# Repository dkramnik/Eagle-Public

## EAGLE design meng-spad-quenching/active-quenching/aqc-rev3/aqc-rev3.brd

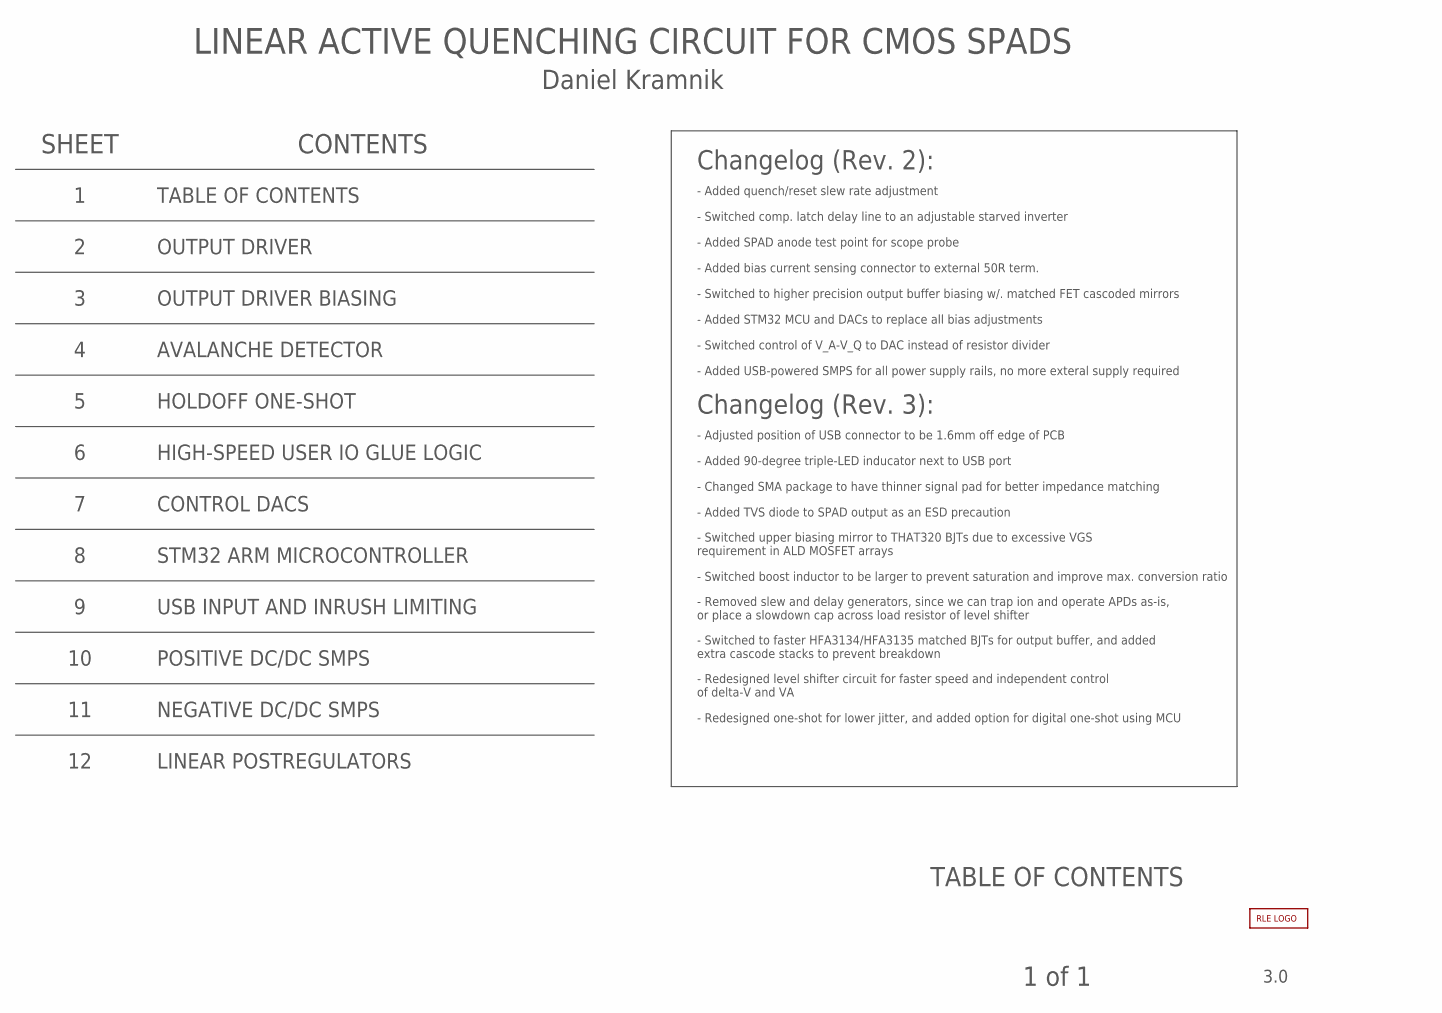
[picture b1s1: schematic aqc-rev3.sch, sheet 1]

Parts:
DNP1000: RLE_LOGO

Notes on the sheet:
Changelog (Rev. 2):
- Added quench/reset slew rate adjustment
- Switched comp. latch delay line to an adjustable starved inverter
- Added SPAD anode test point for scope probe
- Added bias current sensing connector to external 50R term.
- Added USB-powered SMPS for all power supply rails, no more exteral supply required
- Added STM32 MCU and DACs to replace all bias adjustments
- Switched to higher precision output buffer biasing w/. matched FET cascoded mirrors
- Switched control of V_A-V_Q to DAC instead of resistor divider
TABLE OF CONTENTS
3.0
1 of 1
LINEAR ACTIVE QUENCHING CIRCUIT FOR CMOS SPADS
SHEET
CONTENTS
Daniel Kramnik
OUTPUT DRIVER
OUTPUT DRIVER BIASING
STM32 ARM MICROCONTROLLER
CONTROL DACS
AVALANCHE DETECTOR
POSITIVE DC/DC SMPS
NEGATIVE DC/DC SMPS
USB INPUT AND INRUSH LIMITING
HOLDOFF ONE-SHOT
LINEAR POSTREGULATORS
Changelog (Rev. 3):
- Adjusted position of USB connector to be 1.6mm off edge of PCB
- Added 90-degree triple-LED inducator next to USB port
- Changed SMA package to have thinner signal pad for better impedance matching
- Added TVS diode to SPAD output as an ESD precaution
- Switched upper biasing mirror to THAT320 BJTs due to excessive VGS requirement in ALD MOSFET arrays
- Switched boost inductor to be larger to prevent saturation and improve max. conversion ratio
- Removed slew and delay generators, since we can trap ion and operate APDs as-is, or place a slowdown cap across load resistor of level shifter
- Switched to faster HFA3134/HFA3135 matched BJTs for output buffer, and added extra cascode stacks to prevent breakdown
- Redesigned level shifter circuit for faster speed and independent control of delta-V and VA
- Redesigned one-shot for lower jitter, and added option for digital one-shot using MCU
HIGH-SPEED USER IO GLUE LOGIC

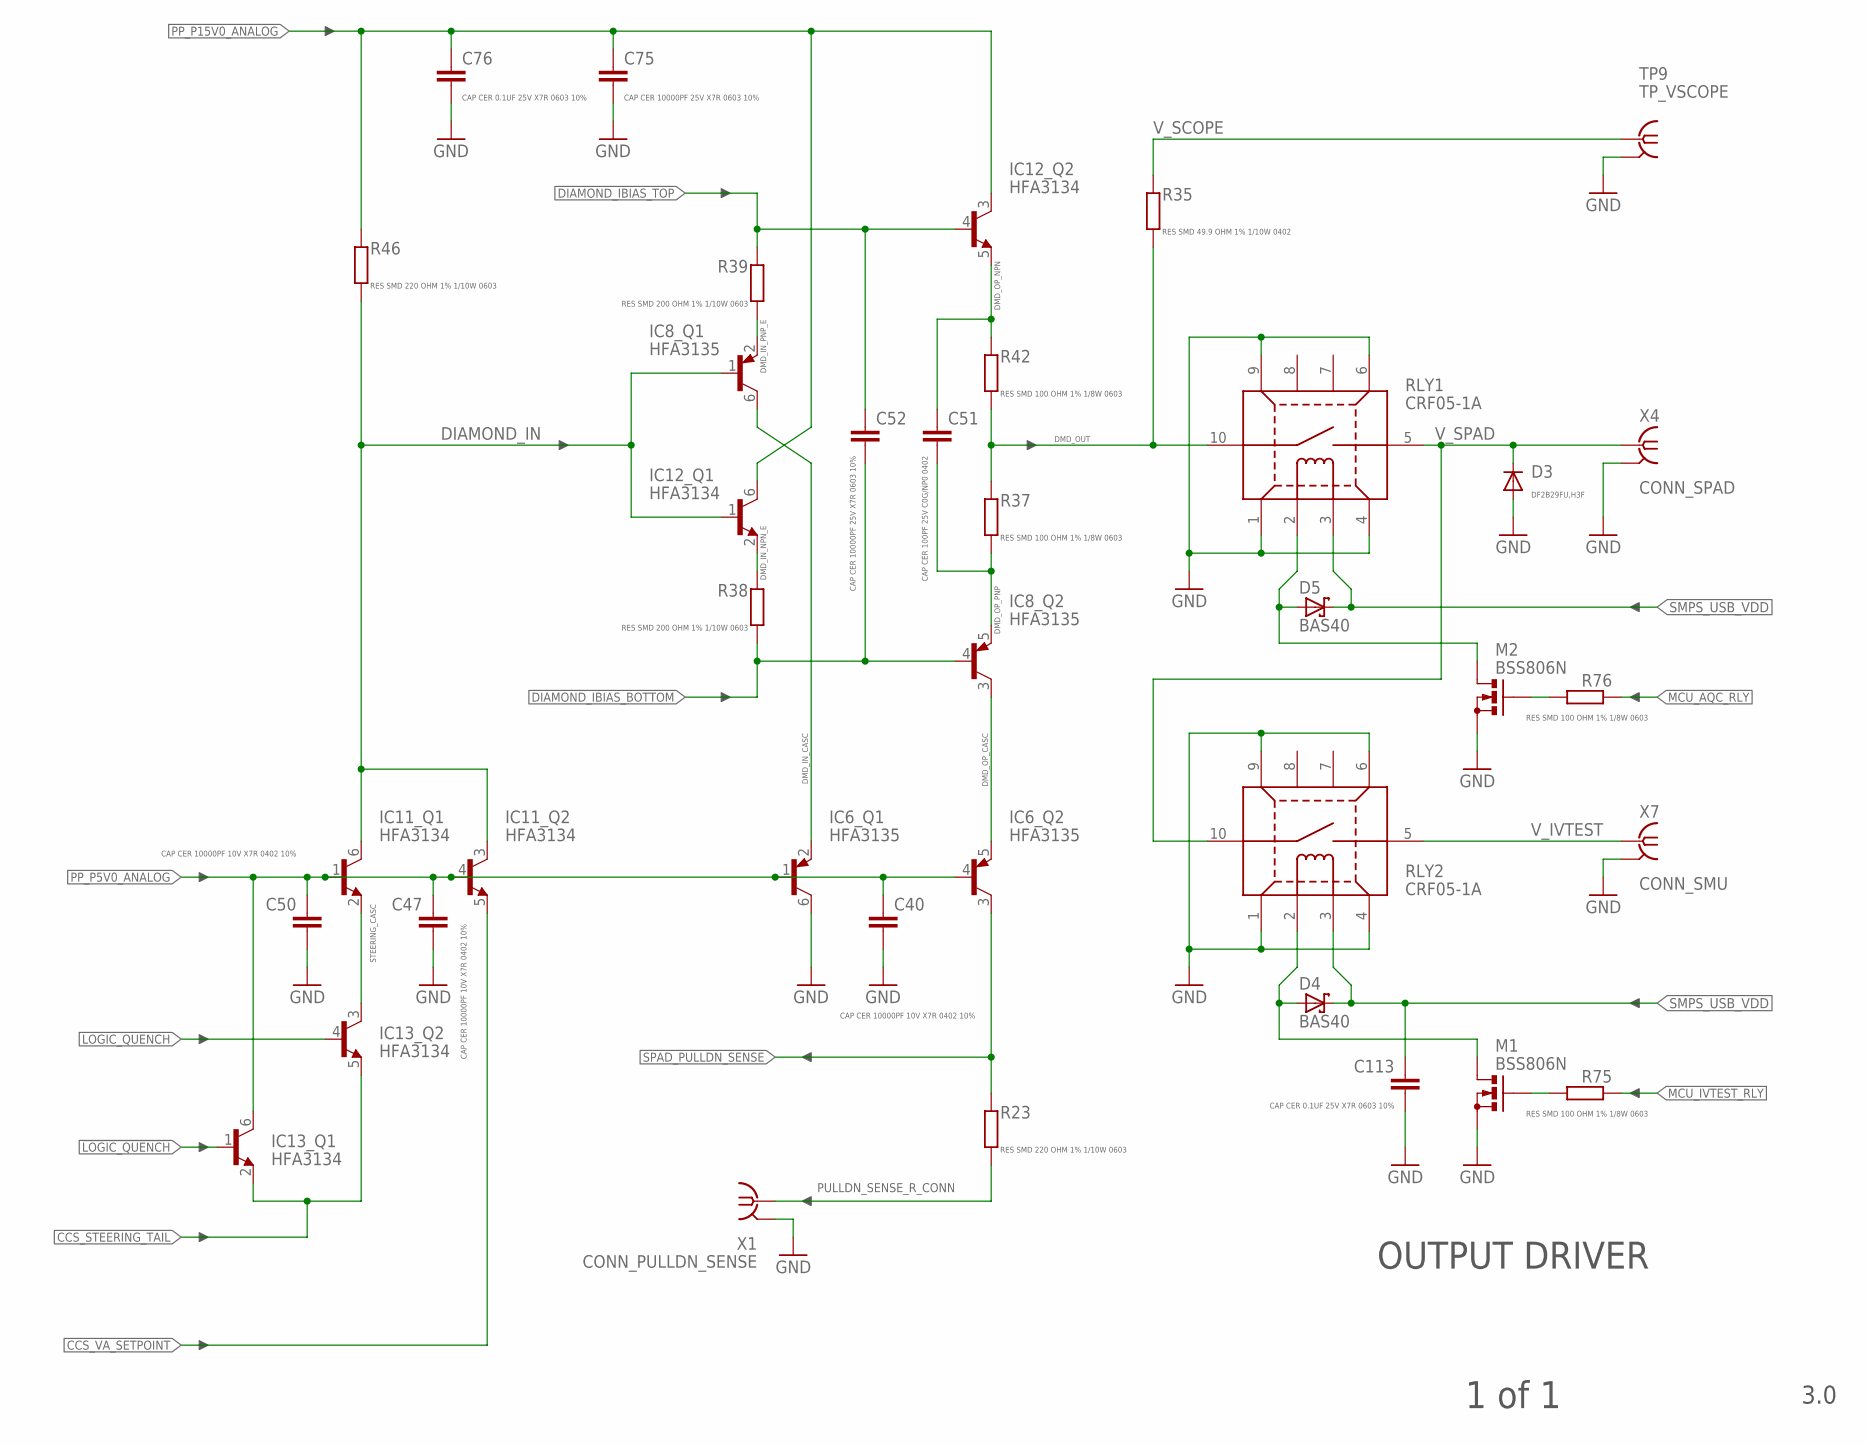
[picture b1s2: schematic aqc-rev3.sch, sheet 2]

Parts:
C40, C47, C50: CAP CER 10000PF 10V X7R 0402 10%; C0402
C51: CAP CER 100PF 25V C0G/NP0 0402; C0402
C52, C75: CAP CER 10000PF 25V X7R 0603 10%; C0603
C76, C113: CAP CER 0.1UF 25V X7R 0603 10%; C0603
D3: DF2B29FU,H3F; SOD523
D4, D5: BAS40; SOT23
IC6, IC8: HFA3135; SOT23-6L
IC11, IC12, IC13: HFA3134; SOT23-6L
M1, M2: BSS806N; SOT23R_INFINEON
R23, R46: RES SMD 220 OHM 1% 1/10W 0603; R0603
R35: RES SMD 49.9 OHM 1% 1/10W 0402; R0402
R37, R42, R75, R76: RES SMD 100 OHM 1% 1/8W 0603; R0603
R38, R39: RES SMD 200 OHM 1% 1/10W 0603; R0603
RLY1, RLY2: CRF05-1A; MEDER_RELAY_CRF
TP9: TP_VSCOPE; JOHNSON-129-0701-30X
X1: CONN_PULLDN_SENSE; J502-ND-142-0701-881/886; MPN 142-0711-871
X4: CONN_SPAD; J502-ND-142-0701-881/886
X7: CONN_SMU; J502-ND-142-0701-881/886

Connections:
!LOGIC_QUENCH: IC13.1 (B); also elsewhere on the board
CCS_STEERING_TAIL: IC13.2 (E), IC13.5 (E); also elsewhere on the board
CCS_VA_SETPOINT: IC11.5 (E); also elsewhere on the board
DIAMOND_IBIAS_BOTTOM: C52.2, IC8.4 (B), R38.1; also elsewhere on the board
DIAMOND_IBIAS_TOP: C52.1, IC12.4 (B), R39.2; also elsewhere on the board
DIAMOND_IN: IC8.1 (B), IC11.3 (C), IC11.6 (C), IC12.1 (B), R46.1
DMD_IN_CASC: IC6.2 (E), IC8.6 (C)
DMD_IN_NPN_E: IC12.2 (E), R38.2
DMD_IN_PNP_E: IC8.2 (E), R39.1
DMD_OP_CASC: IC6.5 (E), IC8.3 (C)
DMD_OP_NPN: C51.1, IC12.5 (E), R42.2
DMD_OP_PNP: C51.2, IC8.5 (E), R37.1
DMD_OUT: R35.1, R37.2, R42.1, RLY1.10 (PIN10)
GND: C40.2, C47.2, C50.2, C75.2, C76.2, C113.2, D3.A, IC6.6 (C), M1.2 (S), M2.2 (S), RLY1.1 (PIN1), RLY1.4 (PIN4), RLY1.6 (PIN6), RLY1.9 (PIN9), RLY2.1 (PIN1), RLY2.4 (PIN4), RLY2.6 (PIN6), RLY2.9 (PIN9), TP9.GND1 (GND), TP9.GND2 (GND), X1.G@1 (GND), X1.G@2 (GND), X1.G@3 (GND), X1.G@4 (GND), X4.G@1 (GND), X4.G@2 (GND), X4.G@3 (GND), X4.G@4 (GND), X7.G@1 (GND), X7.G@2 (GND), X7.G@3 (GND), X7.G@4 (GND); also elsewhere on the board
LOGIC_QUENCH: IC13.4 (B); also elsewhere on the board
MCU_AQC_RLY: R76.2; also elsewhere on the board
MCU_IVTEST_RLY: R75.2; also elsewhere on the board
unnamed: M2.1 (G), R76.1
unnamed: D5.1 (A), M2.3 (D), RLY1.2 (PIN2)
unnamed: D4.1 (A), M1.3 (D), RLY2.2 (PIN2)
unnamed: M1.1 (G), R75.1
PP_P5V0_ANALOG: C40.1, C47.1, C50.1, IC6.1 (B), IC6.4 (B), IC11.1 (B), IC11.4 (B), IC13.6 (C); also elsewhere on the board
PP_P15V0_ANALOG: C75.1, C76.1, IC12.3 (C), IC12.6 (C), R46.2; also elsewhere on the board
PULLDN_SENSE_R_CONN: R23.1, X1.1
SMPS_USB_VDD: C113.1, D4.3 (C), D5.3 (C), RLY1.3 (PIN3), RLY2.3 (PIN3); also elsewhere on the board
SPAD_PULLDN_SENSE: IC6.3 (C), R23.2; also elsewhere on the board
STEERING_CASC: IC11.2 (E), IC13.3 (C)
V_IVTEST: RLY2.5 (PIN5), X7.1
V_SCOPE: R35.2, TP9.SIG (1)
V_SPAD: D3.C, RLY1.5 (PIN5), RLY2.10 (PIN10), X4.1

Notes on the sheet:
OUTPUT DRIVER
3.0
1 of 1

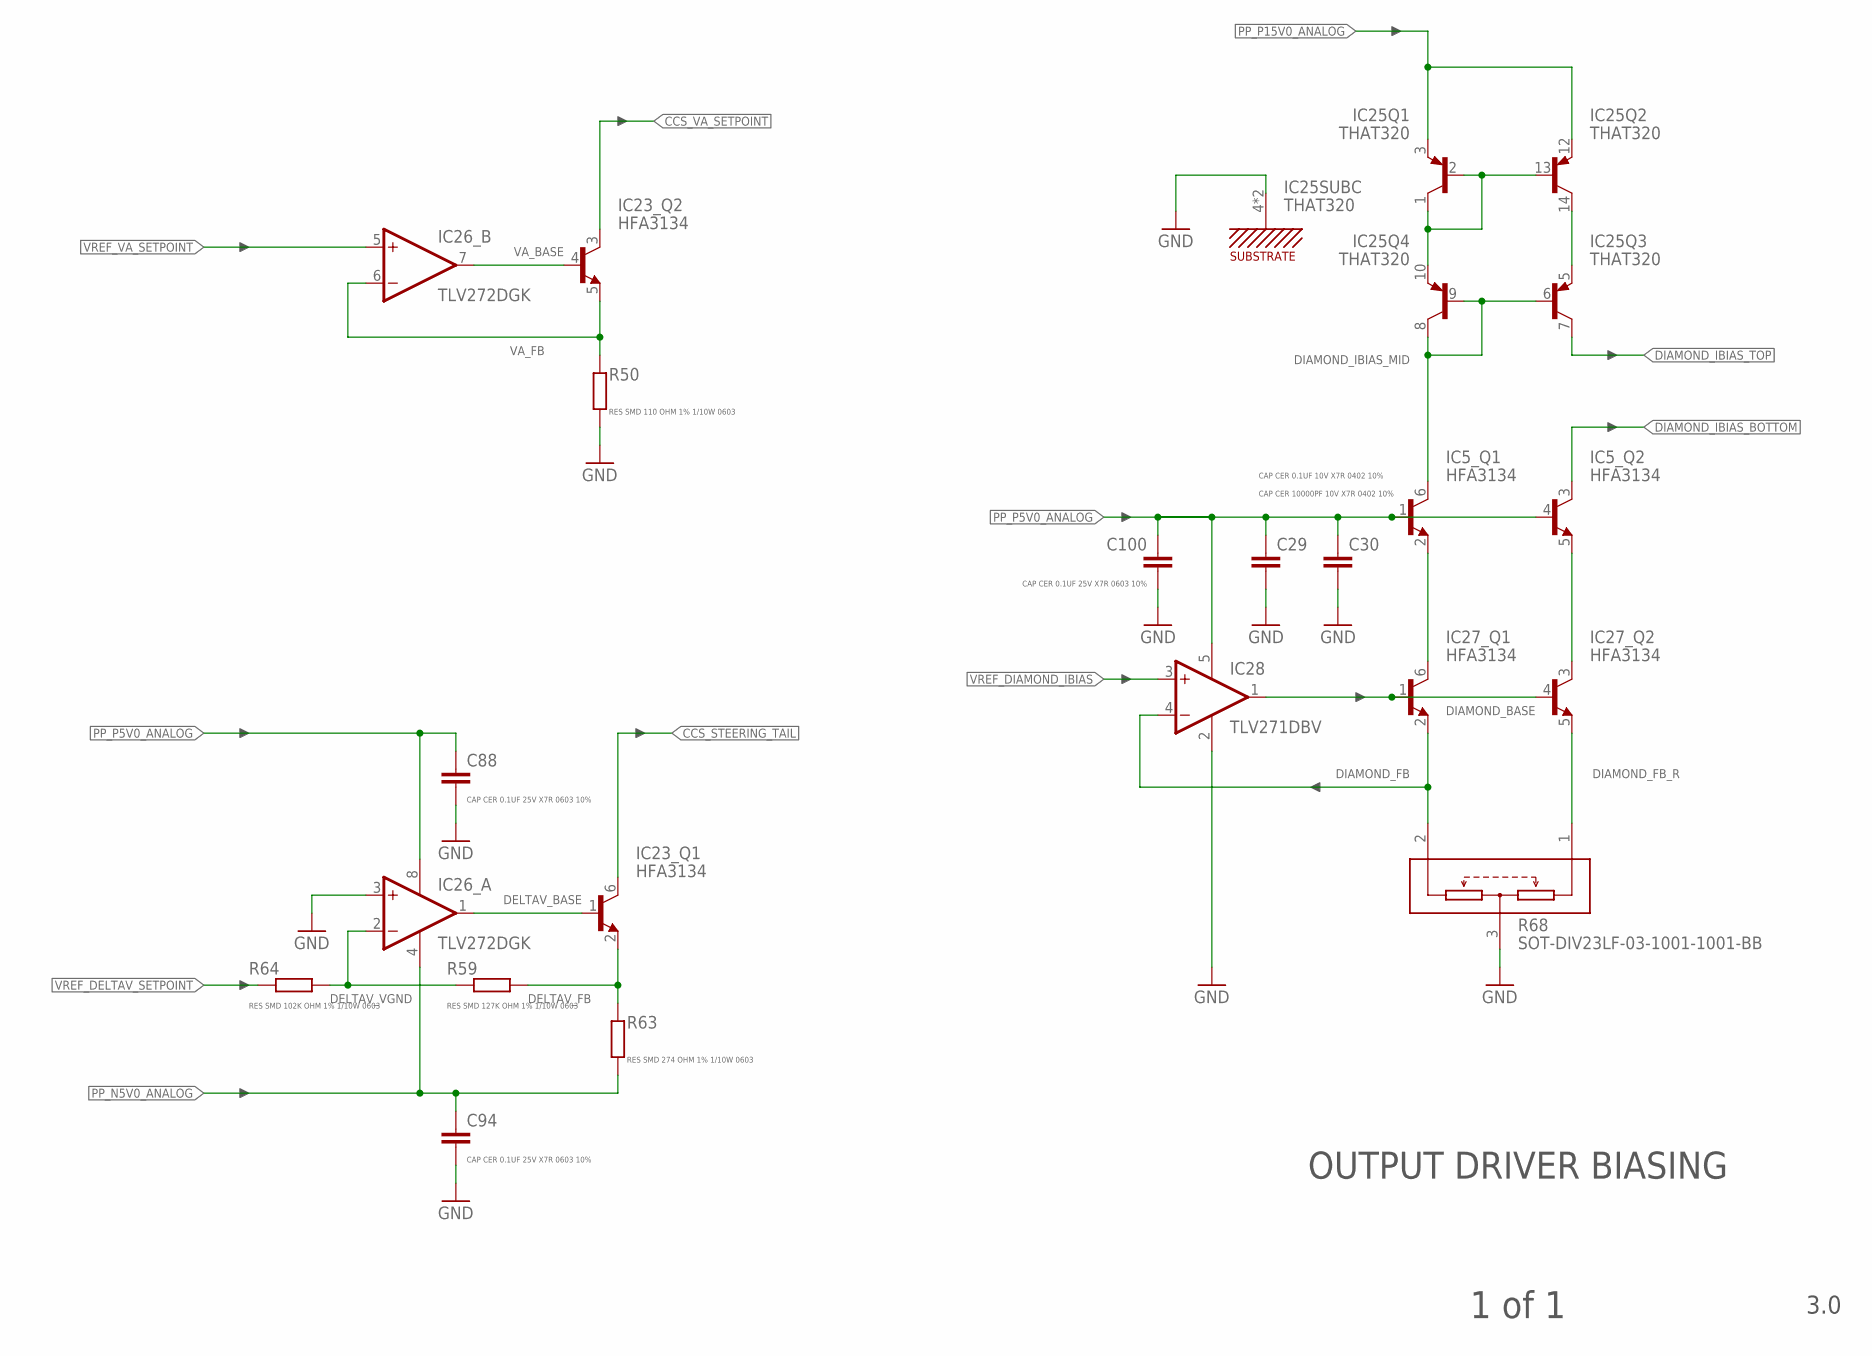
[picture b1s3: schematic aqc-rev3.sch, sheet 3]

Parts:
C29: CAP CER 0.1UF 10V X7R 0402 10%; C0402
C30: CAP CER 10000PF 10V X7R 0402 10%; C0402
C88, C94, C100: CAP CER 0.1UF 25V X7R 0603 10%; C0603
IC5, IC23, IC27: HFA3134; SOT23-6L
IC25: THAT320; SO14
IC26: TLV272DGK; MSOP8
IC28: TLV271DBV; SOT23-5
R50: RES SMD 110 OHM 1% 1/10W 0603; R0603
R59: RES SMD 127K OHM 1% 1/10W 0603; R0603
R63: RES SMD 274 OHM 1% 1/10W 0603; R0603
R64: RES SMD 102K OHM 1% 1/10W 0603; R0603
R68: SOT-DIV23LF-03-1001-1001-BB; SOT23C

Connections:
CCS_STEERING_TAIL: IC23.6 (C); also elsewhere on the board
CCS_VA_SETPOINT: IC23.3 (C); also elsewhere on the board
DELTAV_BASE: IC23.1 (B), IC26.1 (OUT)
DELTAV_FB: IC23.2 (E), R59.1, R63.2
DELTAV_VGND: IC26.2 (-IN), R59.2, R64.1
DIAMOND_BASE: IC27.1 (B), IC27.4 (B), IC28.1 (OUT)
DIAMOND_FB: IC27.2 (E), IC28.4 (-IN), R68.2 (TOP)
DIAMOND_FB_R: IC27.5 (E), R68.1 (BOTTOM)
DIAMOND_IBIAS_BOTTOM: IC5.3 (C); also elsewhere on the board
DIAMOND_IBIAS_MID: IC5.6 (C), IC25.6 (B), IC25.8 (C), IC25.9 (B)
DIAMOND_IBIAS_TOP: IC25.7 (C); also elsewhere on the board
GND: C29.2, C30.2, C88.2, C94.2, C100.2, IC25.4 (SUBC), IC25.11 (SUBC), IC26.3 (+IN), IC28.2 (V-), R50.1, R68.3 (MIDDLE); also elsewhere on the board
unnamed: IC5.2 (E), IC27.6 (C)
unnamed: IC5.5 (E), IC27.3 (C)
unnamed: IC25.1 (C), IC25.2 (B), IC25.10 (E), IC25.13 (B)
unnamed: IC25.5 (E), IC25.14 (C)
PP_N5V0_ANALOG: C94.1, IC26.4 (V-), R63.1; also elsewhere on the board
PP_P5V0_ANALOG: C29.1, C30.1, C88.1, C100.1, IC5.1 (B), IC5.4 (B), IC26.8 (V+), IC28.5 (V+); also elsewhere on the board
PP_P15V0_ANALOG: IC25.3 (E), IC25.12 (E); also elsewhere on the board
VA_BASE: IC23.4 (B), IC26.7 (OUT)
VA_FB: IC23.5 (E), IC26.6 (-IN), R50.2
VREF_DELTAV_SETPOINT: R64.2; also elsewhere on the board
VREF_DIAMOND_IBIAS: IC28.3 (+IN); also elsewhere on the board
VREF_VA_SETPOINT: IC26.5 (+IN); also elsewhere on the board

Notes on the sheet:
OUTPUT DRIVER BIASING
3.0
1 of 1

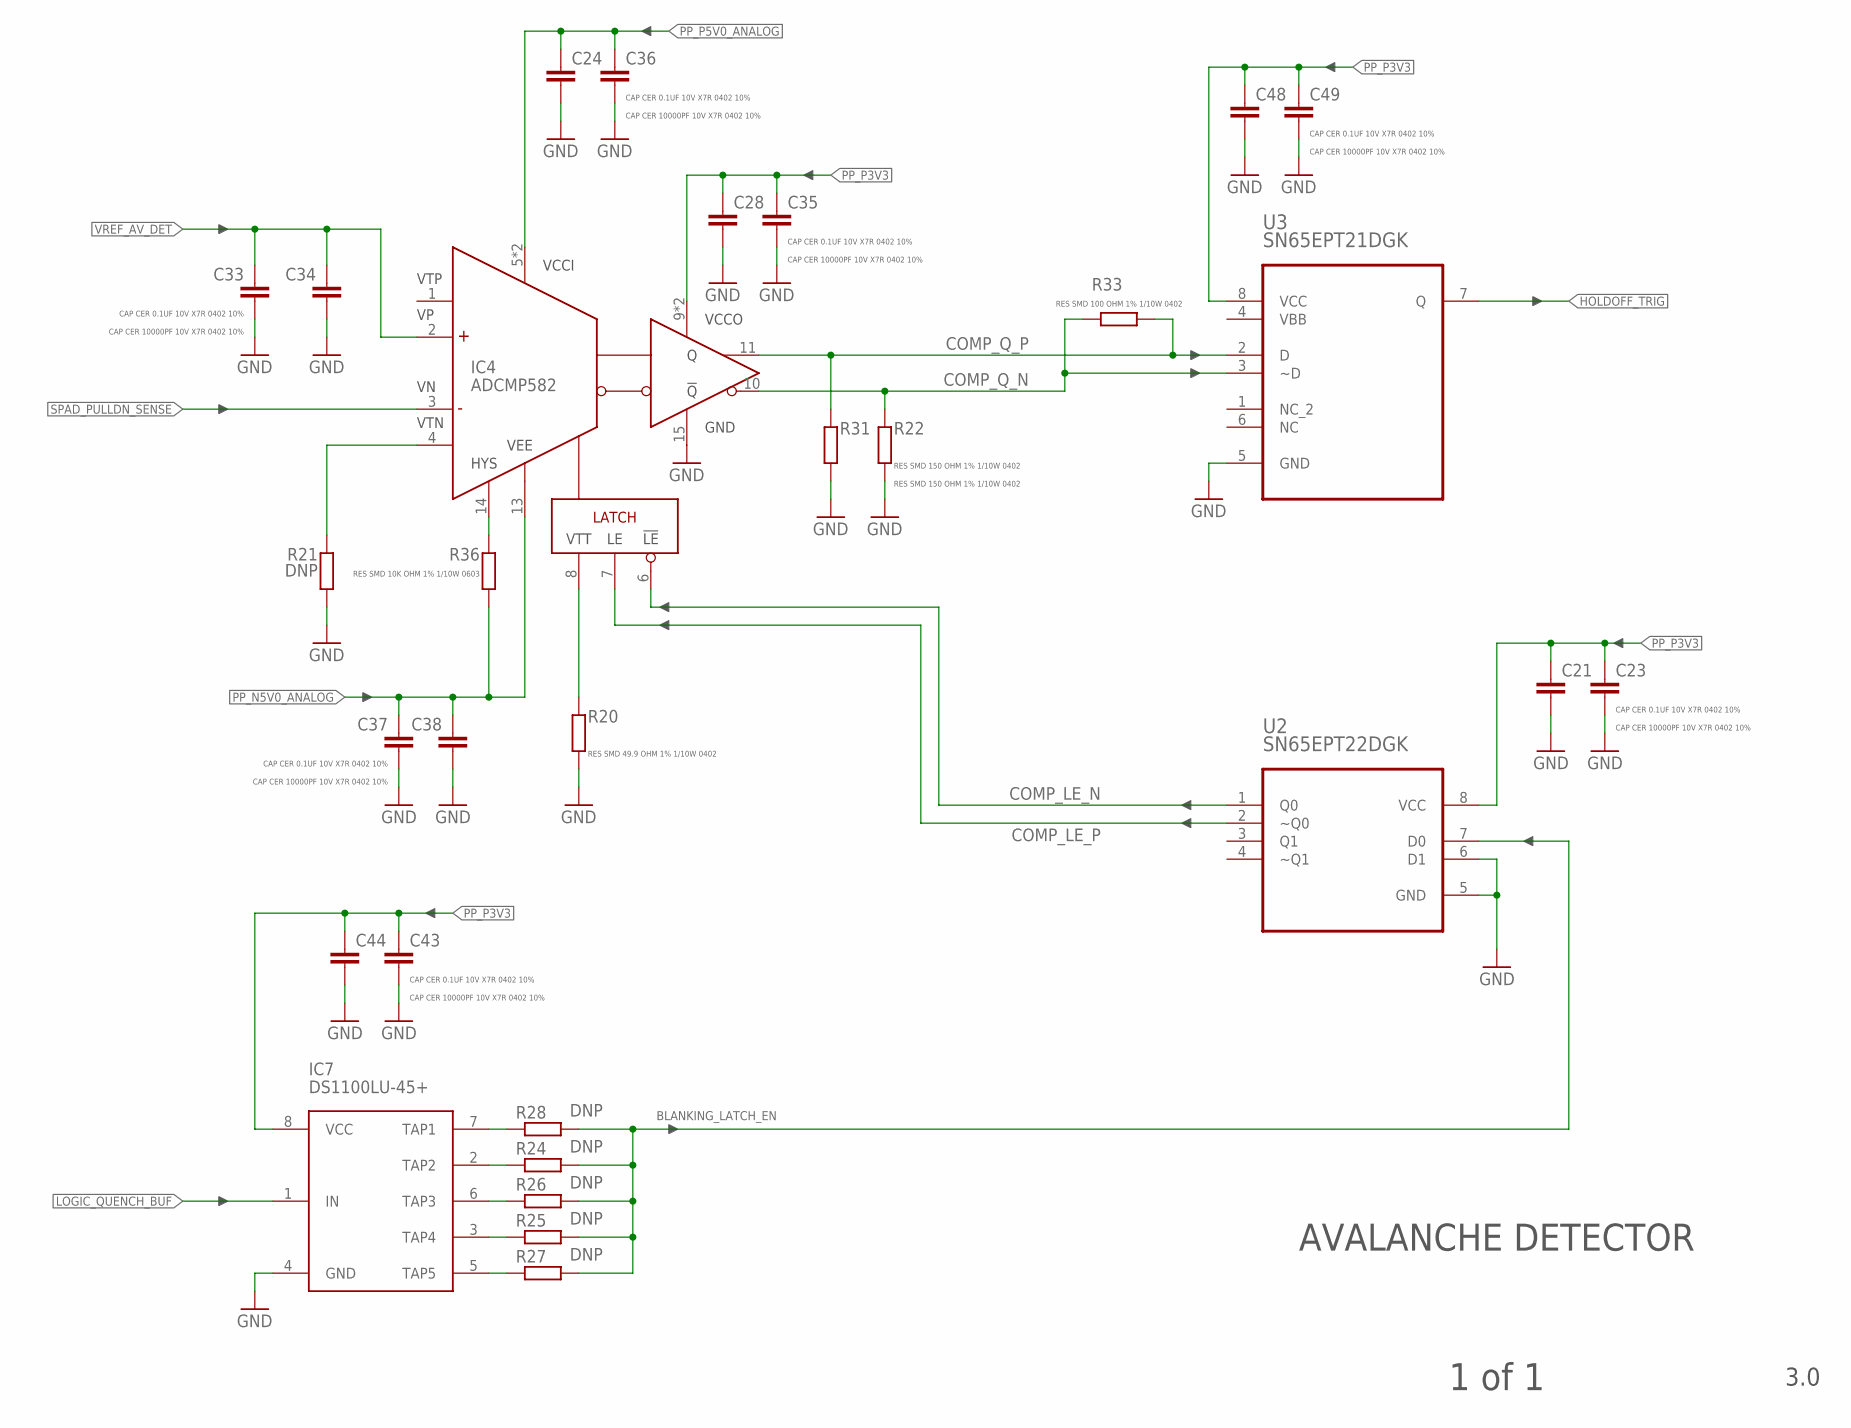
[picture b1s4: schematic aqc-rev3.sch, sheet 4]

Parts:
C21, C24, C28, C34, C38, C44, C48: CAP CER 10000PF 10V X7R 0402 10%; C0402
C23, C33, C35, C36, C37, C43, C49: CAP CER 0.1UF 10V X7R 0402 10%; C0402
IC4: ADCMP582; QFN50P300X300X80-16N
IC7: DS1100LU-45+; MSOP8
R20: RES SMD 49.9 OHM 1% 1/10W 0402; R0402
R21, R24, R25, R26, R27, R28: DNP; R0603
R22, R31: RES SMD 150 OHM 1% 1/10W 0402; R0402
R33: RES SMD 100 OHM 1% 1/10W 0402; R0402
R36: RES SMD 10K OHM 1% 1/10W 0603; R0603
U2: SN65EPT22DGK; SOP65P490X110-8N
U3: SN65EPT21DGK; SOP65P490X110-8N

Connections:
BLANKING_LATCH_EN: R24.1, R25.1, R26.1, R27.1, R28.1, U2.7 (D0)
COMP_HYS: IC4.14 (HYS), R36.2
COMP_LE_N: IC4.6 (!LE), U2.1 (Q0)
COMP_LE_P: IC4.7 (LE), U2.2 (~Q0)
COMP_Q_N: IC4.10 (!Q), R22.1, R33.1, U3.3 (~D)
COMP_Q_P: IC4.11 (Q), R31.1, R33.2, U3.2 (D)
COMP_VTN: IC4.4 (VTN), R21.2
COMP_VTT: IC4.8 (VTT), R20.1
GND: C21.2, C23.2, C24.2, C28.2, C33.2, C34.2, C35.2, C36.2, C37.2, C38.2, C43.2, C44.2, C48.2, C49.2, IC4.15 (GND), IC7.4 (GND), R20.2, R21.1, R22.2, R31.2, U2.5 (GND), U2.6 (D1), U3.5 (GND); also elsewhere on the board
HOLDOFF_TRIG: U3.7 (Q); also elsewhere on the board
LOGIC_QUENCH_BUF: IC7.1 (IN); also elsewhere on the board
PP_N5V0_ANALOG: C37.1, C38.1, IC4.13 (VEE), R36.1; also elsewhere on the board
PP_P3V3: C21.1, C23.1, C28.1, C35.1, C43.1, C44.1, C48.1, C49.1, IC4.9 (VCCO), IC4.12 (VCCO), IC7.8 (VCC), U2.8 (VCC), U3.8 (VCC); also elsewhere on the board
PP_P5V0_ANALOG: C24.1, C36.1, IC4.5 (VCCI), IC4.16 (VCCI); also elsewhere on the board
SPAD_PULLDN_SENSE: IC4.3 (VN); also elsewhere on the board
TAP1: IC7.7 (TAP1), R28.2
TAP2: IC7.2 (TAP2), R24.2
TAP3: IC7.6 (TAP3), R26.2
TAP4: IC7.3 (TAP4), R25.2
TAP5: IC7.5 (TAP5), R27.2
VBB: U3.4 (VBB)
VREF_AV_DET: C33.1, C34.1, IC4.2 (VP); also elsewhere on the board

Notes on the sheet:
AVALANCHE DETECTOR
3.0
1 of 1

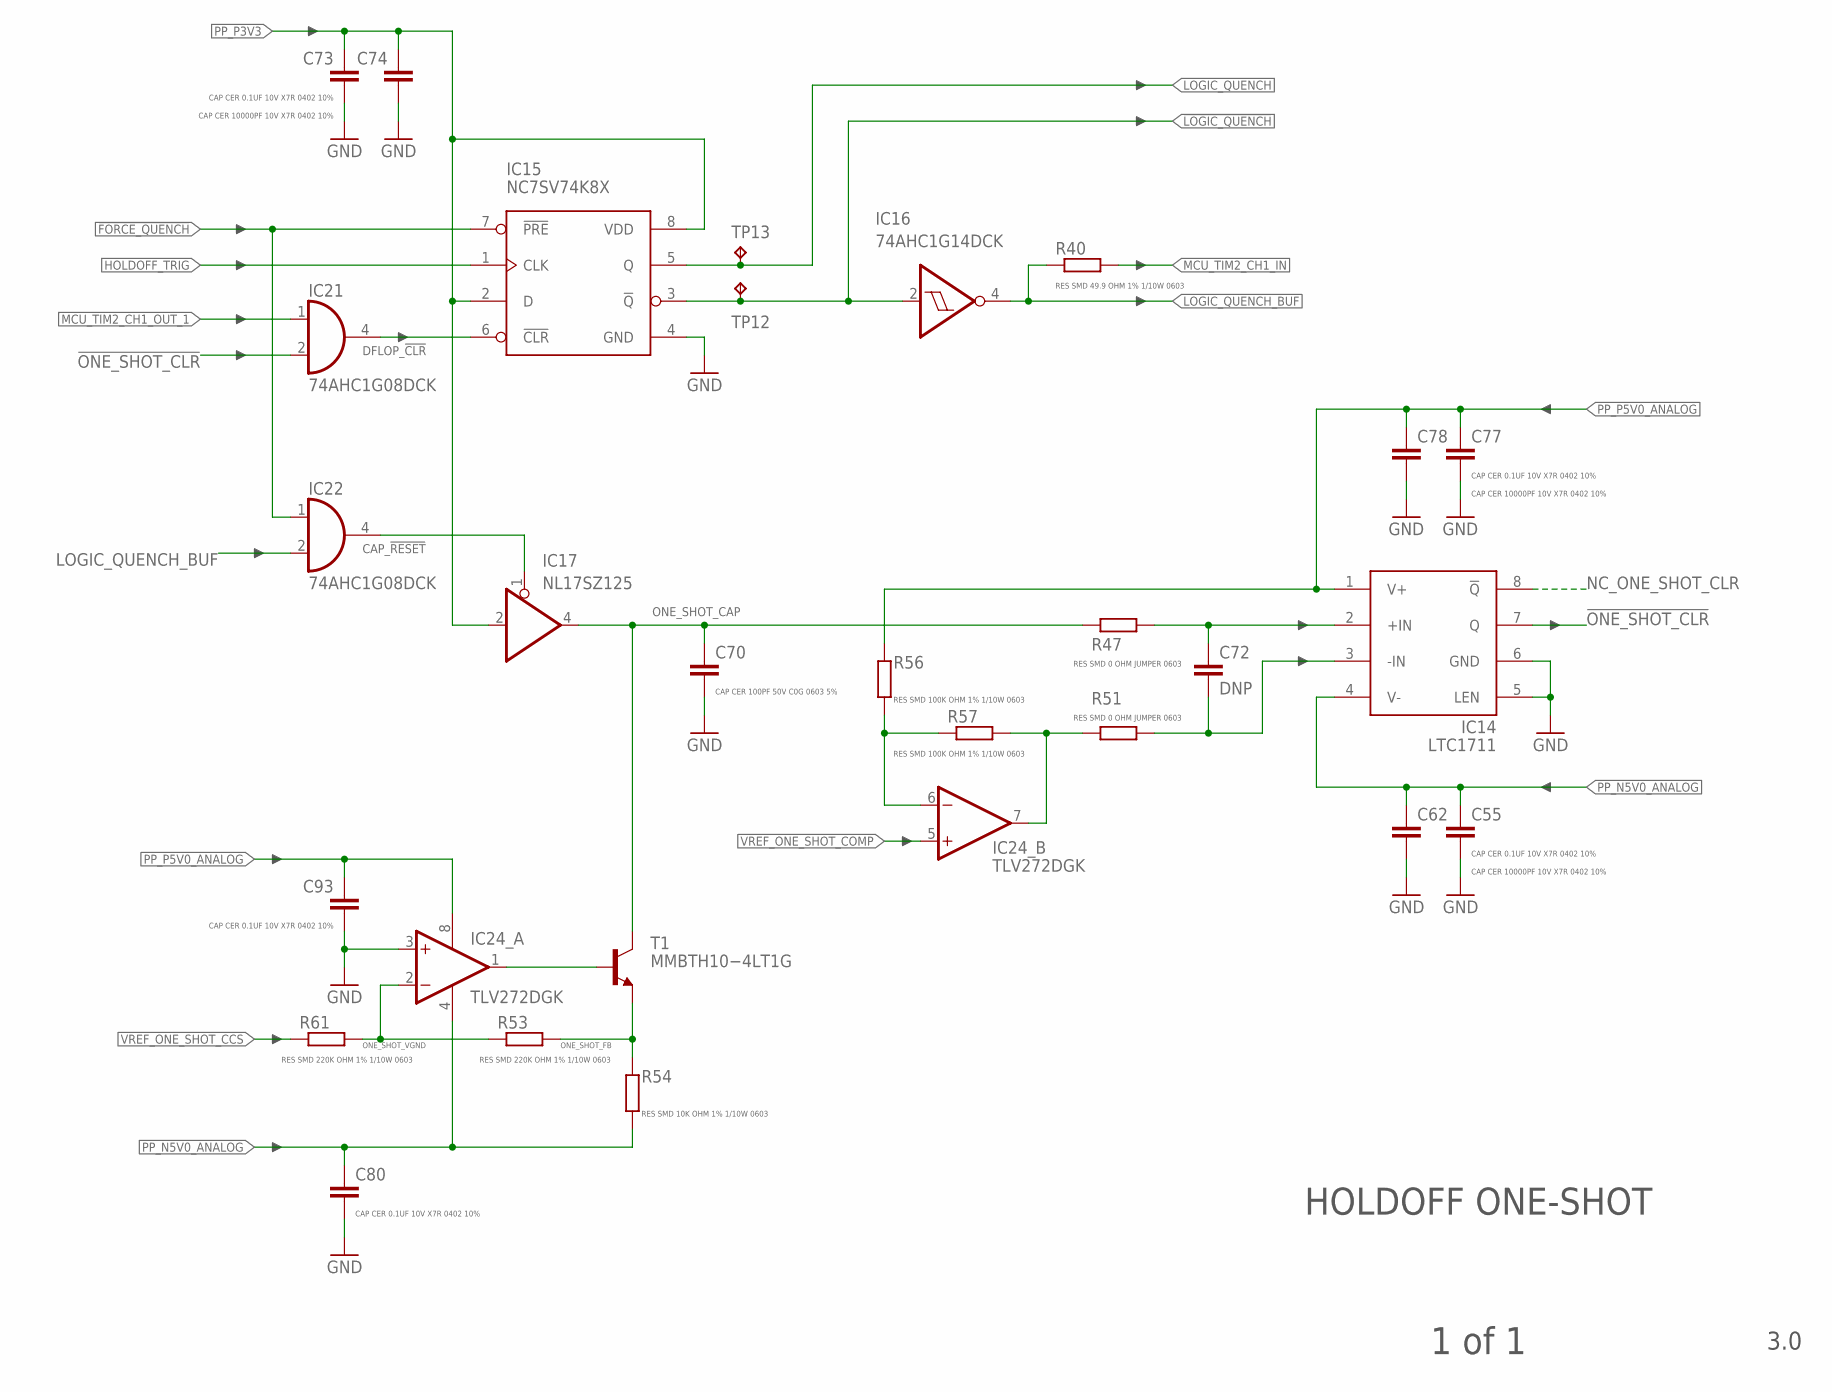
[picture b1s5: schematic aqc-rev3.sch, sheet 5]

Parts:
C55, C73, C77, C80, C93: CAP CER 0.1UF 10V X7R 0402 10%; C0402
C62, C74, C78: CAP CER 10000PF 10V X7R 0402 10%; C0402
C70: CAP CER 100PF 50V C0G 0603 5%; C0603
C72: DNP; C0402
IC14: LTC1711; MSOP8
IC15: NC7SV74K8X; US8_3.1MM_JDEC_MO-187
IC16: 74AHC1G14DCK; SC70-5
IC17: NL17SZ125; SC70-5
IC21, IC22: 74AHC1G08DCK; SC70-5
IC24: TLV272DGK; MSOP8
R40: RES SMD 49.9 OHM 1% 1/10W 0603; R0603
R47, R51: RES SMD 0 OHM JUMPER 0603; R0603
R53, R61: RES SMD 220K OHM 1% 1/10W 0603; R0603
R54: RES SMD 10K OHM 1% 1/10W 0603; R0603
R56, R57: RES SMD 100K OHM 1% 1/10W 0603; R0603
T1: MMBTH10−4LT1G; SOT23-BEC
TP12, TP13: TPTP06R; TP06R

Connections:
!FORCE_QUENCH: IC15.7 (!PRE), IC22.1 (I0); also elsewhere on the board
!LOGIC_QUENCH: IC15.3 (!Q), IC16.2 (I), TP12.TP; also elsewhere on the board
!ONE_SHOT_CLR: IC14.7 (Q), IC21.2 (I1)
CAP_!RESET: IC17.1 (OE), IC22.4 (O)
DFLOP_!CLR: IC15.6 (!CLR), IC21.4 (O)
GND: C55.2, C62.2, C70.2, C73.2, C74.2, C77.2, C78.2, C80.2, C93.2, IC14.5 (LEN), IC14.6 (GND), IC15.4 (GND), IC24.3 (+IN); also elsewhere on the board
HOLDOFF_TRIG: IC15.1 (CLK); also elsewhere on the board
LOGIC_QUENCH: IC15.5 (Q), TP13.TP; also elsewhere on the board
LOGIC_QUENCH_BUF: IC16.4 (O), IC22.2 (I1), R40.2; also elsewhere on the board
MCU_TIM2_CH1_IN: R40.1; also elsewhere on the board
MCU_TIM2_CH1_OUT_1: IC21.1 (I0); also elsewhere on the board
unnamed: IC24.1 (OUT), T1.B
unnamed: IC24.7 (OUT), R51.2, R57.1
unnamed: IC24.6 (-IN), R56.1, R57.2
unnamed: C72.2, IC14.3 (-IN), R51.1
unnamed: C72.1, IC14.2 (+IN), R47.1
NC_ONE_SHOT_CLR: IC14.8 (!Q)
ONE_SHOT_CAP: C70.1, IC17.4 (O), R47.2, T1.C
ONE_SHOT_FB: R53.1, R54.1, T1.E
ONE_SHOT_VGND: IC24.2 (-IN), R53.2, R61.1
PP_N5V0_ANALOG: C55.1, C62.1, C80.1, IC14.4 (V-), IC24.4 (V-), R54.2; also elsewhere on the board
PP_P3V3: C73.1, C74.1, IC15.2 (D), IC15.8 (VDD), IC17.2 (I); also elsewhere on the board
PP_P5V0_ANALOG: C77.1, C78.1, C93.1, IC14.1 (V+), IC24.8 (V+), R56.2; also elsewhere on the board
VREF_ONE_SHOT_CCS: R61.2; also elsewhere on the board
VREF_ONE_SHOT_COMP: IC24.5 (+IN); also elsewhere on the board

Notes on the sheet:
HOLDOFF ONE-SHOT
3.0
1 of 1

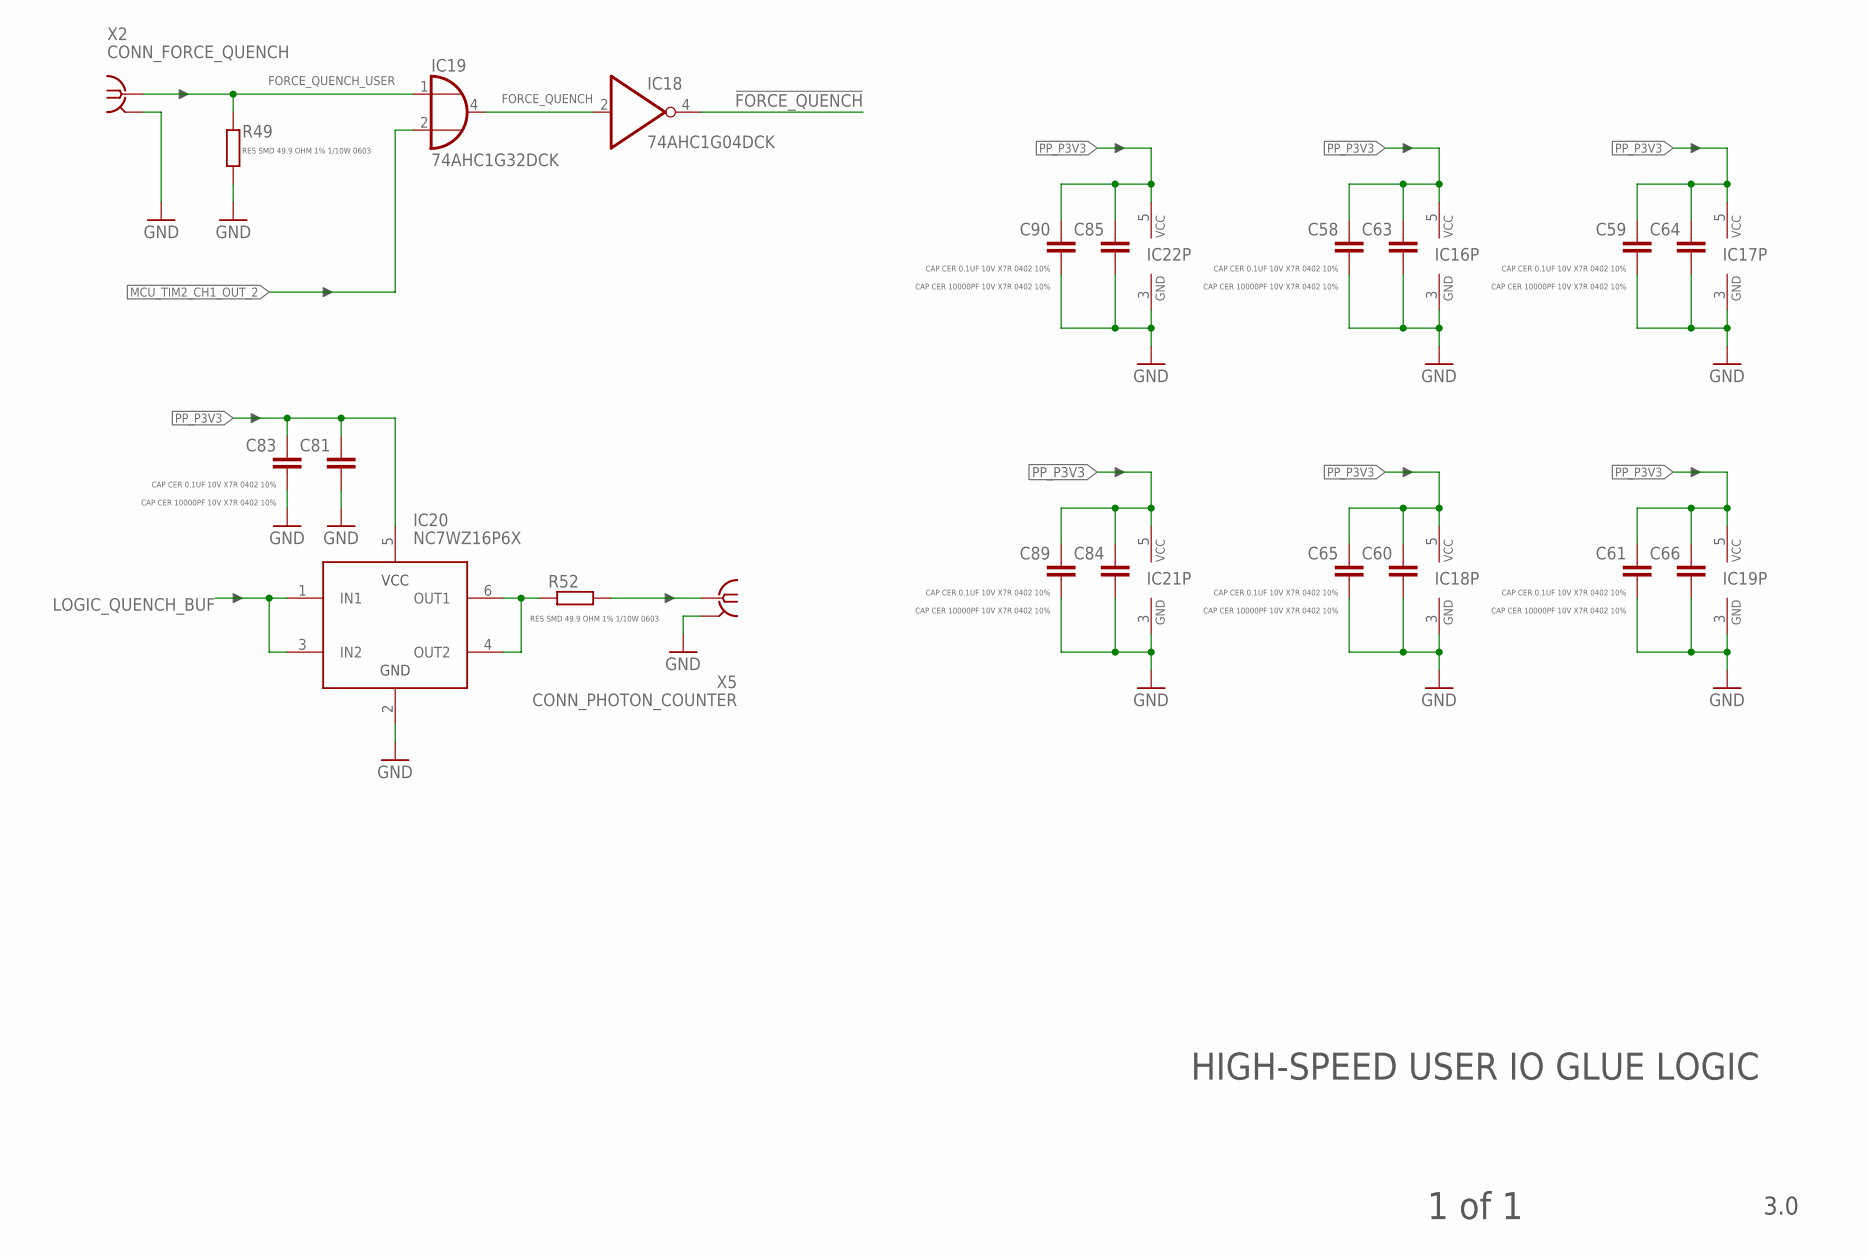
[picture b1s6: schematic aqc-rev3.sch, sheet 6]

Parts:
C58, C59, C61, C65, C83, C89, C90: CAP CER 0.1UF 10V X7R 0402 10%; C0402
C60, C63, C64, C66, C81, C84, C85: CAP CER 10000PF 10V X7R 0402 10%; C0402
IC16: 74AHC1G14DCK; SC70-5
IC17: NL17SZ125; SC70-5
IC18: 74AHC1G04DCK; SC70-5
IC19: 74AHC1G32DCK; SC70-5
IC20: NC7WZ16P6X; SC70-6L
IC21, IC22: 74AHC1G08DCK; SC70-5
R49, R52: RES SMD 49.9 OHM 1% 1/10W 0603; R0603
X2: CONN_FORCE_QUENCH; J502-ND-142-0701-881/886; MPN 142-0711-871
X5: CONN_PHOTON_COUNTER; J502-ND-142-0701-881/886

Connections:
!FORCE_QUENCH: IC18.4 (O); also elsewhere on the board
FORCE_QUENCH: IC18.2 (I), IC19.4 (O)
FORCE_QUENCH_USER: IC19.1 (I0), R49.2, X2.1
GND: C58.2, C59.2, C60.2, C61.2, C63.2, C64.2, C65.2, C66.2, C81.2, C83.2, C84.2, C85.2, C89.2, C90.2, IC16.3 (GND), IC17.3 (GND), IC18.3 (GND), IC19.3 (GND), IC20.2 (GND), IC21.3 (GND), IC22.3 (GND), R49.1, X2.G@1 (GND), X2.G@2 (GND), X2.G@3 (GND), X2.G@4 (GND), X5.G@1 (GND), X5.G@2 (GND), X5.G@3 (GND), X5.G@4 (GND); also elsewhere on the board
LOGIC_QUENCH_BUF: IC20.1 (IN1), IC20.3 (IN2); also elsewhere on the board
MCU_TIM2_CH1_OUT_2: IC19.2 (I1); also elsewhere on the board
unnamed: IC20.4 (OUT2), IC20.6 (OUT1), R52.2
PHOTON_COUNT_OUT: R52.1, X5.1
PP_P3V3: C58.1, C59.1, C60.1, C61.1, C63.1, C64.1, C65.1, C66.1, C81.1, C83.1, C84.1, C85.1, C89.1, C90.1, IC16.5 (VCC), IC17.5 (VCC), IC18.5 (VCC), IC19.5 (VCC), IC20.5 (VCC), IC21.5 (VCC), IC22.5 (VCC); also elsewhere on the board

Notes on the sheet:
HIGH-SPEED USER IO GLUE LOGIC
3.0
1 of 1

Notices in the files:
parts and their libraries:
microbuilder: This work is placed in the public domain, and may be freely used for commercial and non-commercial work with the following conditions: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
SparkFun-Connectors: Licensing: Creative Commons ShareAlike 4.0 International - https://creativecommons.org/licenses/by-sa/4.0
